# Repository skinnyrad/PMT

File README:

Poor Man's Tracker

GPS:
- Contains an ESP32 project for the ESPIDF development toolkit to be flashed onto an ESP32 microcontroller.
  This code was used to read incoming NMEA data from our uBLOX m8 GPS receiver. This project simply prints out the data as text.

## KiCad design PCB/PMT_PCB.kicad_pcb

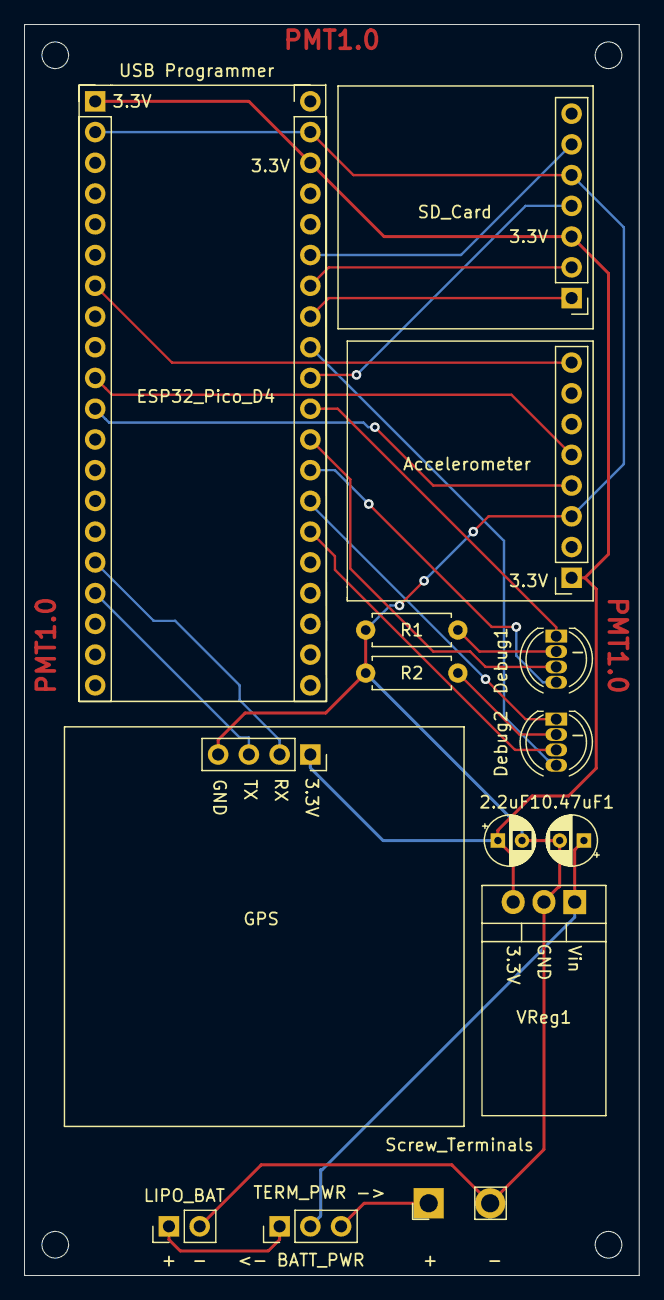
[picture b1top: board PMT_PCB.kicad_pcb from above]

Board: 2 copper layers, 50.8 x 103.4 mm, 14 parts (0 on the bottom side), 22 nets.

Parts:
0.47uF1, 2.2uF1: Capacitor; CP_Radial_D4.0mm_P2.00mm
Accelerometer: Conn_01x08; Accelerometer_Breakout
Debug1, Debug2: LED_RGB; LED_D5.0mm-4_RGB
ESP32_Pico_D4: ESP32_Pico_D4
GPS: Conn_01x04; GPS
LIPO_BAT: Conn_01x02; PinHeader_1x02_P2.54mm_Vertical
R1, R2: 100 ohm; R_Axial_DIN0207_L6.3mm_D2.5mm_P7.62mm_Horizontal
SD_Card: Conn_01x07; SD_Card_Breakout
Screw_Terminals: Screw_Terminals
Slide_Switch: Slide_Switch; PinHeader_1x03_P2.54mm_Vertical
VReg1: AZ2940; TO-220-3_Vertical

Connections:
3.3V: 2.2uF1.1, Accelerometer.1, ESP32_Pico_D4.1, ESP32_Pico_D4.38, GPS.1, SD_Card.3, VReg1.3
3.7-12Vin: 0.47uF1.1, Slide_Switch.2, VReg1.1
ACCEL_INT1: Accelerometer.8, ESP32_Pico_D4.7
ACCEL_SCL: Accelerometer.4, ESP32_Pico_D4.11
ACCEL_SDA: Accelerometer.5, ESP32_Pico_D4.10
Blue1: Debug1.4, ESP32_Pico_D4.28
Blue2: Debug2.4, ESP32_Pico_D4.32
GND: 0.47uF1.2, 2.2uF1.2, Accelerometer.3, ESP32_Pico_D4.2, ESP32_Pico_D4.39, GPS.4, LIPO_BAT.2, R1.1, R2.1, SD_Card.5, Screw_Terminals.2, VReg1.2
GPS_RX: ESP32_Pico_D4.16, GPS.2
GPS_TX: ESP32_Pico_D4.17, GPS.3
Green1: Debug1.3, ESP32_Pico_D4.29
Green2: Debug2.3, ESP32_Pico_D4.26
LIPO_PWR: LIPO_BAT.1, Slide_Switch.1
unnamed: Debug1.2, R1.2
unnamed: Debug2.2, R2.2
Red1: Debug1.1, ESP32_Pico_D4.30
Red2: Debug2.1, ESP32_Pico_D4.27
SD_CS: ESP32_Pico_D4.33, SD_Card.1
SD_DI: ESP32_Pico_D4.34, SD_Card.2
SD_DO: ESP32_Pico_D4.35, SD_Card.6
SD_SCK: ESP32_Pico_D4.31, SD_Card.4
Screw_Term_PWR: Screw_Terminals.1, Slide_Switch.3

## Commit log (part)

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2019-12-29 Simplified GPS code
2019-12-29 SD Card Code
2019-12-29 Scan. Connect. Bypass. Drop
    Scan. Connect. Bypass. Drop
2019-12-29 Uploaded Code for GPS and SD card
2019-12-30 Fixed linker issues for SD Card and GPS
2019-12-30 Efficient Open Network connection with unexpected disconnection handling
2019-12-31 Added gitignore
2019-12-31 Added git ignore
2019-12-31 git ignore added for GPS
2019-12-31 binary_to_text update
2019-12-31 Update sd card
2019-12-31 Small Update
2019-12-31 Updated GPS Parsing
2020-01-01 Updated GPS: Simplified UTC Parse function
2020-01-01 Updated GPS: Added Latitude Parsing
2020-01-01 Update GPS: Added date parser
2020-01-02 GPS Updates
2020-01-09 Welcome to the microPyrton city
2020-01-09 remove python
2020-01-09 Welcome to the uPy Worldgit add .!
2020-01-09 uPy header
2020-01-09 Scan connect and Post Request
2020-01-09 remove gapi
2020-01-09 test data posting
2020-01-10 csv data out
2020-01-11 feat(structure): restructure uPy files as a python package
2020-01-11 rename factory file
2020-01-12 feat(gps): integrate gps code into package
2020-01-12 replace continue with pass
2020-01-13 load live data from gps and post to server
2020-01-13 handle {} case
2020-01-13 add destructor to handle graceul shutdown
2020-01-13 sd card writer
2020-01-14 add error checking to make sure that RMC data is whole
2020-01-14 remove print
2020-01-14 feat(gps): integrate gps code into package (#5)
    * feat(gps): integrate gps code into package
    * replace continue with pass
    * load live data from gps and post to server
    * handle {} case
    * add destructor to handle graceul shutdown
    * add error checking to make sure that RMC data is whole
2020-01-17 php_1_16_2020
2020-01-17 feat(PHP): commit PHP server code to version control (#7)
2020-01-17 socket test
2020-01-21 parser library
2020-01-21 redirection fix
2020-01-21 remove test file
2020-01-21 feat(SD): Integrate SD card code (#6)
2020-01-24 Accelerometer Code
2020-01-24 Accelerometer
2020-01-26 redirect parsing
2020-01-28 Accelerometer increased calibration
2020-01-29 Dunkin bypassed
2020-02-11 simple logger phase 1
2020-02-13 feat(fsm): create working fsm
2020-02-13 refactor(kml): move kml generation server side
2020-02-13 refactor(kml): move kml generation server side (#14)
2020-02-13 map final, error handling
2020-02-13 Added PIN NUMBERS
2020-02-13 fix import statement
2020-02-13 refactor(gps): remove newline from data and delimit with comma
2020-02-13 feat(logger): implement python logging to log default info and wifi info
2020-02-13 add post logger and remove logger_errors struct from reqst.py
2020-02-18 web red
2020-02-18 full slider with clikc event zoom
2020-02-18 more feats
2020-02-19 encryption init
2020-02-23 aes encryption + local decryption and view of data
2020-02-23 add of user key prompt
2020-02-23 latest PHP files + handling of encrypted data
2020-02-25 feat(gps):added conditional to remove data that isn't outside of a 20m region
2020-02-25 feat(encryption):add aes encryption (#18)
2020-02-25 micropython project Latest commit b169904
2020-02-27 initial integration
2020-02-27 remove micropythono c files
2020-02-27 add post_url to config file
2020-02-27 remove config access with variable
2020-02-27 rename config fields in code
2020-02-27 remove old code
2020-02-27 chore(integration):integrate a working fsm (#23)
    * feat(logger): implement python logging to log default info and wifi info
2020-02-27 comment logging out
2020-02-27 local upload,table fix
2020-02-27 wifi logger commented
2020-02-27 remove logging code (#25)
2020-02-27 one more
2020-02-27 one more comment for logging (#26)
2020-02-27 fix typo in function call (#27)
2020-02-27 latest PHP files, handle encryption post
2020-02-27 fix gps data
2020-02-27 fix GPS indexes (#29)
2020-02-28 feat(logging):implement logging capabilities
2020-02-29 VM update. micropython dev env
2020-03-02 requested changes and a few tested changes
2020-03-02 VM update. micropython dev env (#31)
2020-03-02 removed micropython. Kept builds only
2020-03-02 removed micropython. Kept builds
2020-03-03 prompt key before page render
2020-03-03 restart on disconnect
2020-03-03 remove files
2020-03-03 chore(wifi): fix loop that connects to another network after successful connection
2020-03-04 chore(wifi): fix loop that connects to another network after successful connection (#34)
2020-03-07 GPSTX UBX protocol (incomplete)
2020-03-07 integrated logging
2020-03-08 hardware timer interrupt
2020-03-08 deinit timer if all good
2020-03-08 timer adjustment
2020-03-09 more
2020-03-09 socket closing
2020-03-10 socket closing fix
2020-03-10 modified files directory
2020-03-10 feat(firmware): add modified files that are built into our modded firmware (#37)
2020-03-10 remove unusued variable
2020-03-10 Timer handler + Socket Closing Error Fix (#36)
2020-03-11 feat(mem): replace all string concats with formats
2020-03-11 sdkconfig
2020-03-11 still broken inf loop
2020-03-11 fix posting data
2020-03-11 new flow
2020-03-11 print statements changes
2020-03-12 splashpage new implementation
2020-03-12 gitignore change
2020-03-12 print
2020-03-12 NEW Splash Page Acquisition & Breaking (#42)
2020-03-13 Software Reset wdt
2020-03-13 wdt with gps intervals
2020-03-13 feat(wdt): add wdt to exit from disconnect loop (#44)
2020-03-13 move wdt to below gps_interval instantiation
2020-03-13 testing day updates
2020-03-13 change host
2020-03-13 quick fix
2020-03-14 feat(wifi): add wifi connectivity statistics script
2020-03-14 let the one liners begin
2020-03-19 chore(refactor): remove mode from config file
2020-03-19 chore(refactor): remove mode from main fsm
2020-03-19 chore(exception): catch multiple exceptions within reqst
2020-03-19 remove operation mode from sd config
2020-03-19 fix(wdt): move wdt to before config and add initial feed
2020-03-19 IPv4 test and DNS Failure error code
2020-03-19 dns resolving timer added
2020-03-20 comments added to functions and HTML
2020-03-20 fix(wifi): wrap scan to mitigate high speed scan runtime error
2020-03-20 chore(reqst): add print statement for skipping dns
2020-03-20 requested changes from david
2020-03-20 whoops no station in post
2020-03-20 fix wdt and sd card integration
2020-03-20 ipv4 code fix with socket handling
2020-03-20 speed threshold for wifi connection
2020-03-20 move ussl out of method
2020-03-21 david errors changed
2020-03-21 remove code duplication
2020-03-21 feat: add System Reset ability
2020-03-21 feat(wifi): add wifi connectivity statistics script (#46)
2020-03-21 refactor(fsm): many changes to please see individual git commit standard messages (#47)
    * feat(wifi): handle status 200 before redirection
    * chore(refactor): remove mode from config file
    * chore(refactor): remove mode from main fsm
    * fix(reqst): remove variable reference after closing and collecting
    * chore(exception): catch multiple exceptions within reqst
    * fix(wdt): move wdt to before config and add initial feed
2020-03-21 feat(wifi): 200 Code redirection
2020-03-21 fix(GDT): fix typos in print statements
2020-03-21 fix(reqst): catch OSError: EHOSTUNREACH error
2020-03-21 fix(reqst): tuple return too many items to unpack
2020-03-21 fix(reqst): array index error
2020-03-21 PCB Revision #2 with fixed Schematic
2020-03-23 feat: add System Reset ability (#48)
    all reviewers approved
2020-03-25 PCB Components moved to top of board
2020-03-25 Turned GPS around
2020-03-25 Added missing trace from Vreg to Capacitor
2020-03-25 feat(sd): add gdt to make sure sd card is mounted
2020-03-25 feat(post): update host to append file path after reading in host name
2020-03-26 feat: full system reset instead of software reset. breaks: if using unmodded firmware with this import (#51)
2020-03-26 change php file
2020-03-26 fix encryption and path to index
2020-03-26 feat(post): update host to append file path after reading in host name (#54)
2020-03-26 chore(buffer): remove unsent buffer only when a successful post occurs
2020-03-26 chore(buffer): remove unsent buffer only when a successful post occurs (#57)
2020-03-26 doc(BOM): create the Bill of Materials for PMT1.0
2020-03-26 Added Slide switch to select either LIPO Battery Power or Terminal Power
2020-03-26 add switch to BOM
2020-03-27 rename to index.php
2020-03-27 configuration file manual
2020-03-27 Added Manufacturing Documentation (Hardware Portion)
2020-03-27 bug fixes, build kml fix
2020-03-30 feat: parse tags and forms from html
2020-03-30 cleaned up
2020-03-30 removed duplicate code
2020-03-30 functionizing
2020-03-30 extra line removed
2020-03-31 added efficiency and functionized
2020-03-31 nitpicky fixes
2020-03-31 fix issue
2020-03-31 feat(blacklist): populate blacklist while scanning for networks to avoid connect loop
2020-03-31 whoops
2020-03-31 feat(Map configs and pmt.conf generation)
2020-03-31 rename to PMT portal, api/map to api/portal
2020-03-31 host json path to global var
2020-03-31 removed duplicate code (#63)
    * removed duplicate code
    * extra line removed
2020-03-31 portal to docs
2020-03-31 added infos
2020-03-31 feat(post): post current data point then post 15 data points from the unsent buffer (#64)
2020-03-31 add comments
2020-04-01 Untested backup of code
2020-04-01 functionaized
2020-04-03 removed legacy implementation
2020-04-05 Update html.py
    remove debugging code and prints.
    Changed variable names
2020-04-06 streamlined?
2020-04-06 header update
2020-04-06 removed print
2020-04-06 changed filename copy/paste typo
2020-04-06 Three frozen modules
2020-04-08 Three frozen modules (#69)
2020-04-08 rough draft splashpage breaking
2020-04-14 user details for local uplaods
2020-04-14 setup manual and user manual
2020-04-15 Correctly resubmits forms at Google Fiber
2020-05-05 updated file structure for new port
2020-05-05 reorganized files into ports
2020-05-07 ported gps.py, logging.py, and gdt.py
2020-05-10 ported more files including reqst.py
2020-05-14 wifi scan & connect
2020-05-14 merged in cleanup changes
2020-05-15 added form resubmission changes to esp32/uPy
2020-05-17 added wifi scanning and connecting abilities to machine.py
2020-05-17 Changes to be committed: new file: raspberrypi/usb_gps_demo/gps_test.py
2020-05-19 more conversion before autoconnection testing
2020-05-19 hopefully fixed file location problems
2020-05-19 changes to GPS.py?
2020-05-19 imports wifi from network, not machine
2020-05-19 fixed openPMTdir
2020-05-21 moving forward with auto-connect
2020-05-22 Fixed parsing issue on request_dns_internet()
2020-05-30 unencrypted posting
2020-06-03 implimented process reboot in gdt. Not incorprated in /py
2020-06-03 process reboot implimented in GDT
2020-06-06 fixing form parsing for Cisco-guest by Whole Foods
2020-06-08 trying to fix dead IPs
2020-06-10 worked well on Cisco0747-guest
2020-06-10 working on KFC
2020-06-10 hopefully fixed pulling old GPS data
2020-06-13 fixed gps buffering old data
2020-06-15 attempt1 fixing blacklisted ssid not disconnecting
2020-06-17 requests driven. head auto redirects
2020-06-18 overhaul of html_parser
2020-06-19 been working on mcdonalds
2020-06-24 The beach update B-)
2020-06-26 fix index out of bounds error for HEAD
2020-06-27 Logs to wifi.log are more informative
2020-06-29 fixed blacklisting exiting python
2020-06-30 Reverting network.py to not shutdown dhcpcd
2020-06-30 working pi hat files
2020-07-02 eliminated dhclient. cleaned up IP acquisistion and release.
2020-07-03 Eliminated end_ip_lease function call when vehicle resumed driving
2020-07-03 Displays and records IP address during successful connection.
2020-07-09 changes made to allow rc.local to work
2020-07-13 Added multi-threading, gps acquisition based on speed, blacklist fixes, blacklist based on time and not speed, file locks, and wifi sleep after complete upload
2020-07-14 Sort APs from strongest to weakest and checks to make sure an ssid is still present before attempting to connect.
2020-07-18 Rescans for APs after an association attempt and elimanates sleep at bottom of wifi thread.
